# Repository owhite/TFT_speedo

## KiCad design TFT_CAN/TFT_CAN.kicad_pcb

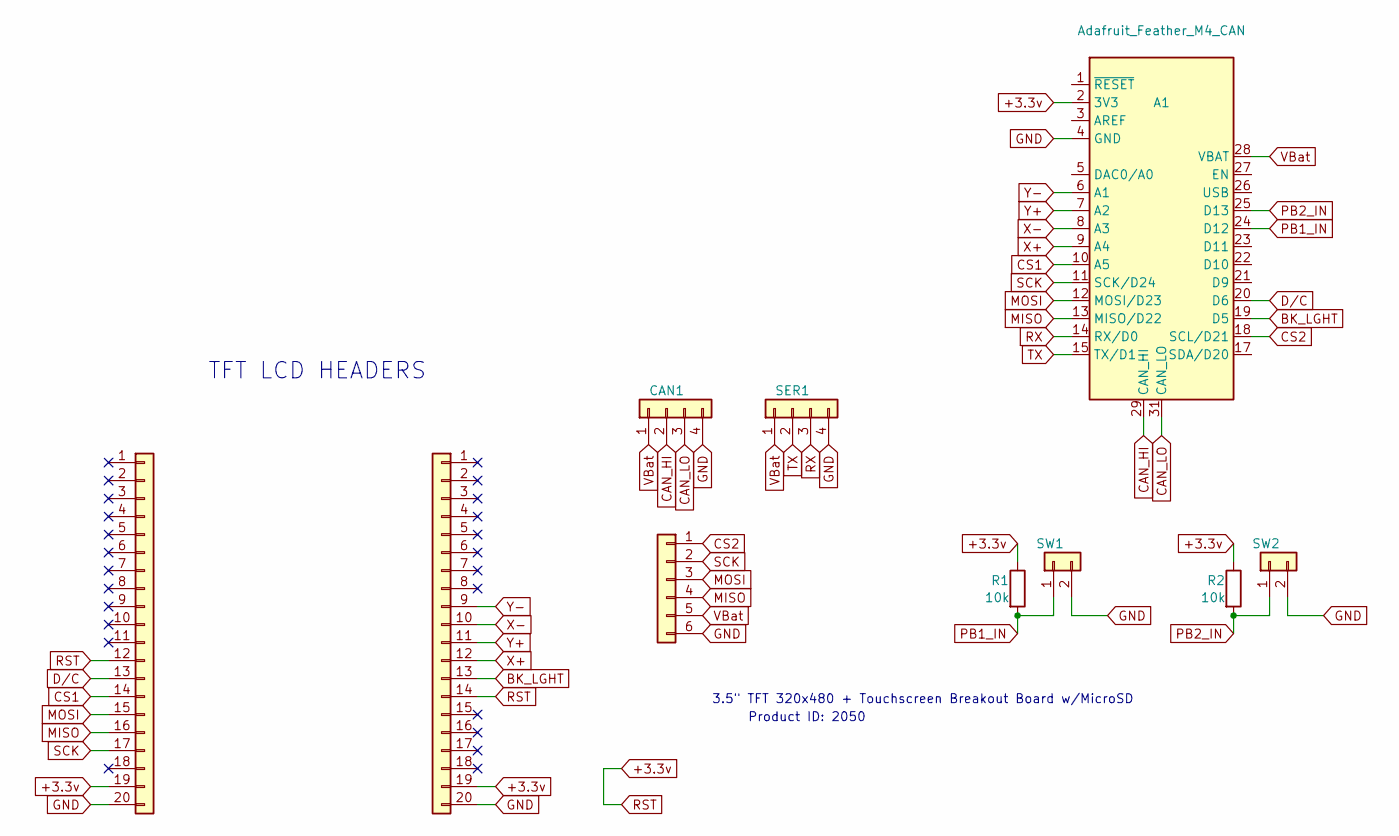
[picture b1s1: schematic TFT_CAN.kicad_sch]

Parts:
A1: Adafruit_Feather_M4_CAN
CAN1: Conn_01x04; my_4_tab_edge
J1, J2: Conn_01x20; PinHeader_1x20_P2.54mm_Vertical
J3: Conn_01x06; PinHeader_1x06_P2.54mm_Vertical
R1, R2: 10k; R_0805_2012Metric
SER1: Conn_01x04; PinHeader_1x04_P2.54mm_Vertical
SW1, SW2: Conn_01x02; PinHeader_1x02_P2.54mm_Vertical

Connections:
+3.3v: A1.2 (3V3), J1.12, J1.19, J2.14, J2.19, R1.1, R2.1
BK_LGHT: A1.19 (D5), J2.13
CAN_HI: A1.29 (CAN_HI), CAN1.2
CAN_LO: A1.31 (CAN_LO), CAN1.3
CS1: A1.10 (A5), J1.14
CS2: A1.18 (SCL/D21), J3.1
D/C: A1.20 (D6), J1.13
GND: A1.4 (GND), CAN1.4, J1.20, J2.20, J3.6, SER1.4, SW1.2, SW2.2
MISO: A1.13 (MISO/D22), J1.16, J3.4
MOSI: A1.12 (MOSI/D23), J1.15, J3.3
PB1_IN: A1.24 (D12), R1.2, SW1.1
PB2_IN: A1.25 (D13), R2.2, SW2.1
RX: A1.14 (RX/D0), SER1.3
SCK: A1.11 (SCK/D24), J1.17, J3.2
TX: A1.15 (TX/D1), SER1.2
VBat: A1.28 (VBAT), CAN1.1, J3.5, SER1.1
X+: A1.9 (A4), J2.12
X-: A1.8 (A3), J2.10
Y+: A1.7 (A2), J2.11
Y-: A1.6 (A1), J2.9

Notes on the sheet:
3.5" TFT 320x480 + Touchscreen Breakout Board w/MicroSD
TFT LCD HEADERS
Product ID: 2050

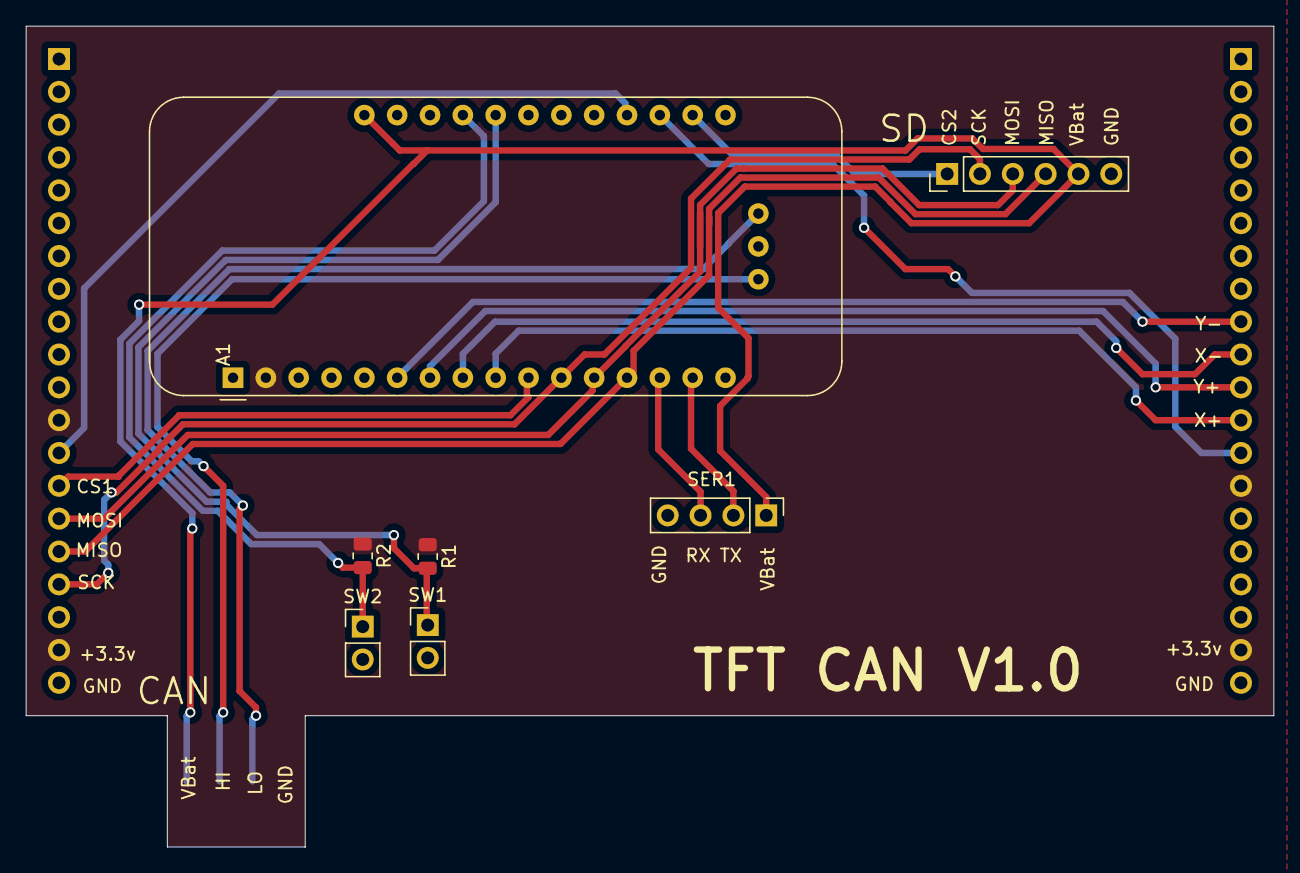
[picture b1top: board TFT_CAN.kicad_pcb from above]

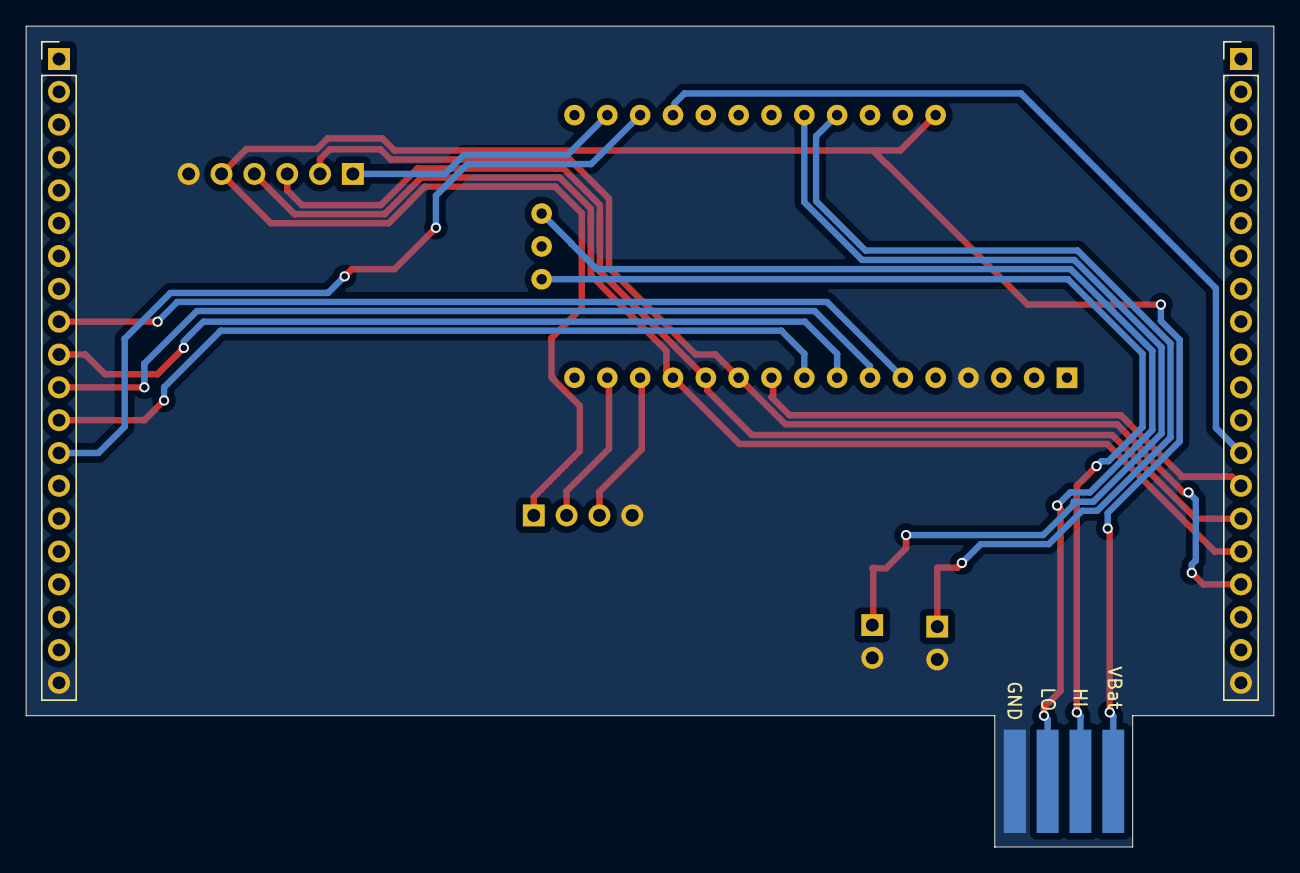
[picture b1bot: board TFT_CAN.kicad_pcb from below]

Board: 2 copper layers, 96.5 x 63.5 mm, 10 parts (3 on the bottom side), 20 nets.

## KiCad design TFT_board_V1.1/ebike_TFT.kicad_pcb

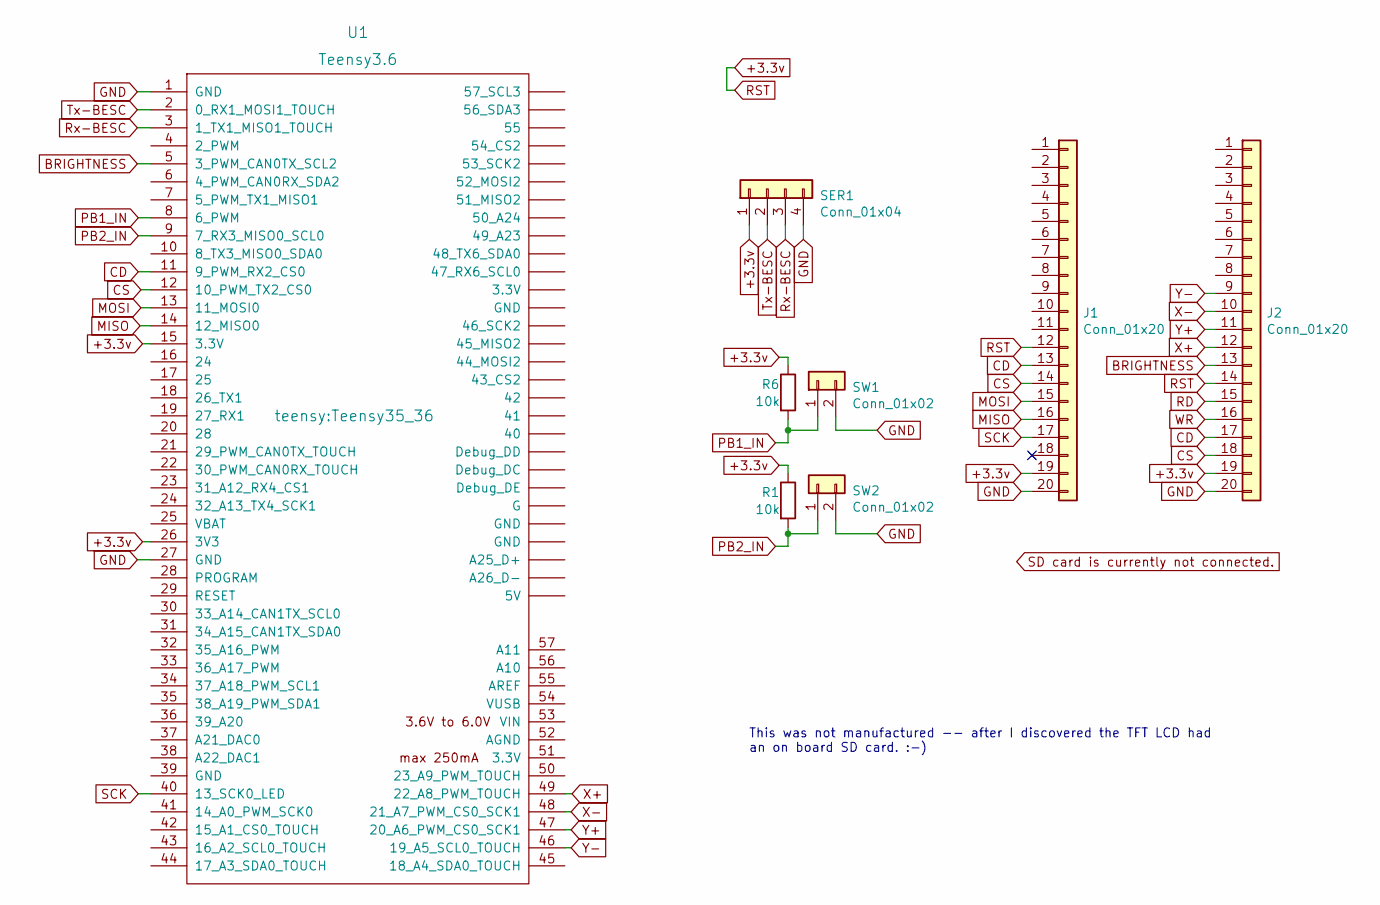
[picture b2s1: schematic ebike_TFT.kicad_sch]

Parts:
J1, J2: Conn_01x20; PinHeader_1x20_P2.54mm_Vertical
R1, R6: 10k; R_0805_2012Metric
SER1: Conn_01x04; PinHeader_1x04_P2.54mm_Vertical
SW1, SW2: Conn_01x02; PinHeader_1x02_P2.54mm_Vertical
U1: Teensy3.6; Teensy35_36

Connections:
+3.3v: J1.12, J1.19, J2.14, J2.19, R1.1, R6.1, SER1.1, U1.15 (3.3V), U1.26 (3V3)
BRIGHTNESS: J2.13, U1.5 (3_PWM_CAN0TX_SCL2)
CD: J1.13, J2.17, U1.11 (9_PWM_RX2_CS0)
CS: J1.14, J2.18, U1.12 (10_PWM_TX2_CS0)
GND: J1.20, J2.20, SER1.4, SW1.2, SW2.2, U1.1 (GND), U1.27 (GND)
MISO: J1.16, U1.14 (12_MISO0)
MOSI: J1.15, U1.13 (11_MOSI0)
PB1_IN: R6.2, SW1.1, U1.8 (6_PWM)
PB2_IN: R1.2, SW2.1, U1.9 (7_RX3_MISO0_SCL0)
RD: J2.15
Rx-BESC: SER1.3, U1.3 (1_TX1_MISO1_TOUCH)
SCK: J1.17, U1.40 (13_SCK0_LED)
Tx-BESC: SER1.2, U1.2 (0_RX1_MOSI1_TOUCH)
WR: J2.16
X+: J2.12, U1.49 (22_A8_PWM_TOUCH)
X-: J2.10, U1.48 (21_A7_PWM_CS0_SCK1)
Y+: J2.11, U1.47 (20_A6_PWM_CS0_SCK1)
Y-: J2.9, U1.46 (19_A5_SCL0_TOUCH)

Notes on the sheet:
This was not manufactured -- after I discovered the TFT LCD had an on board SD card. :-)

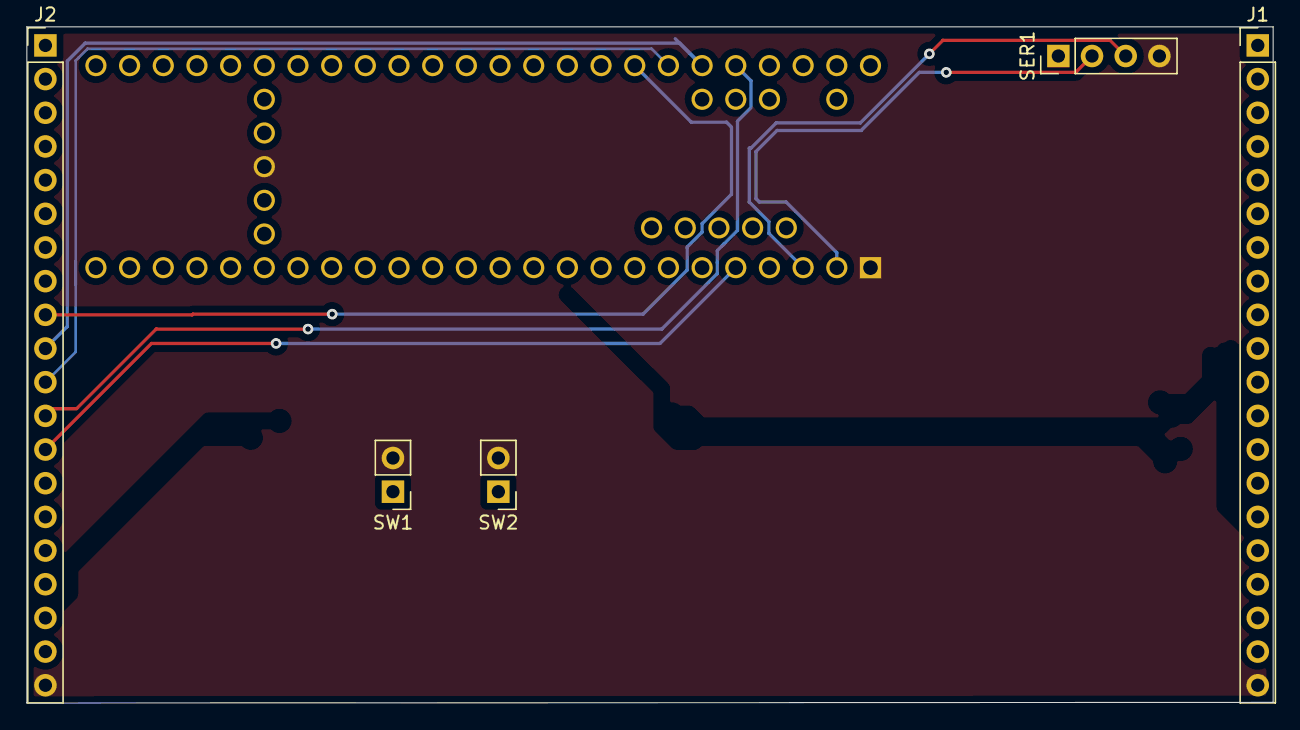
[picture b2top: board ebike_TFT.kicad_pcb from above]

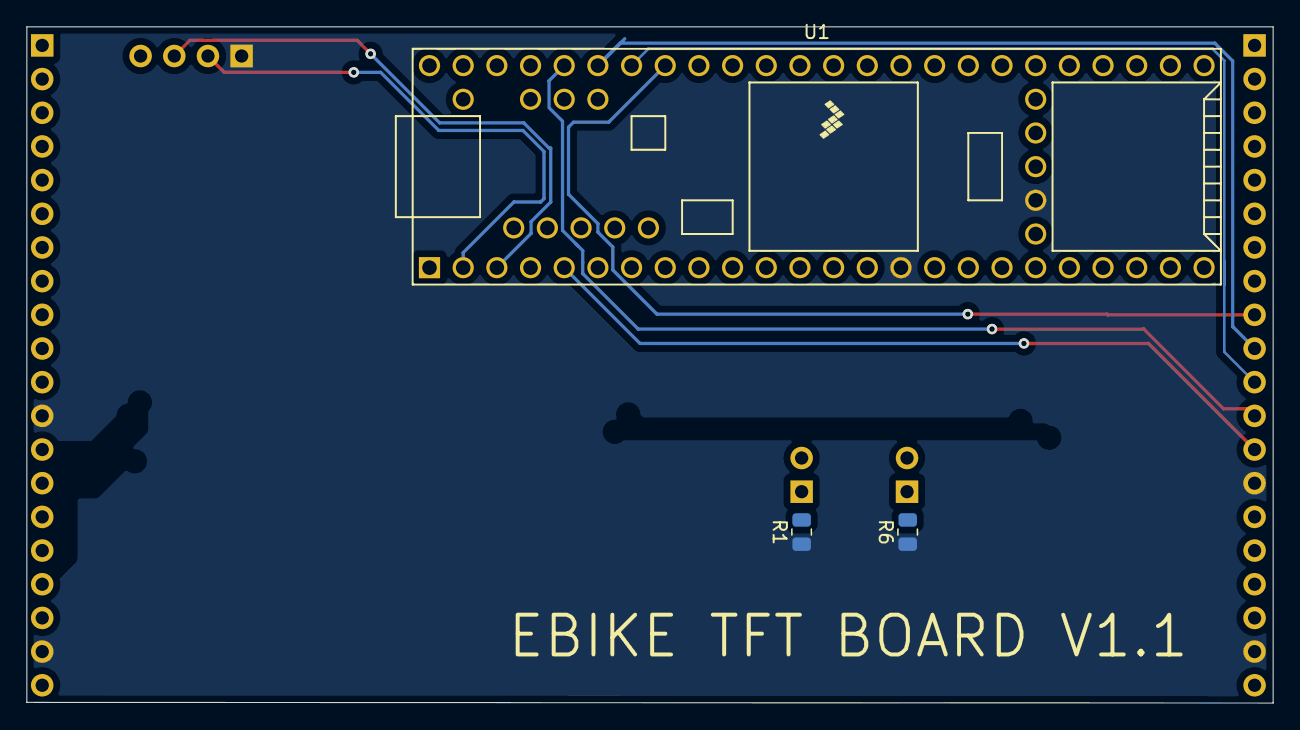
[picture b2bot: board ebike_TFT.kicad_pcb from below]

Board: 2 copper layers, 94.0 x 51.0 mm, 8 parts (3 on the bottom side), 16 nets.

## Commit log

2023-04-26 Create license
2023-04-27 finished layout
2023-04-27 final cosmetic stuff
2023-04-27 PCBway order
